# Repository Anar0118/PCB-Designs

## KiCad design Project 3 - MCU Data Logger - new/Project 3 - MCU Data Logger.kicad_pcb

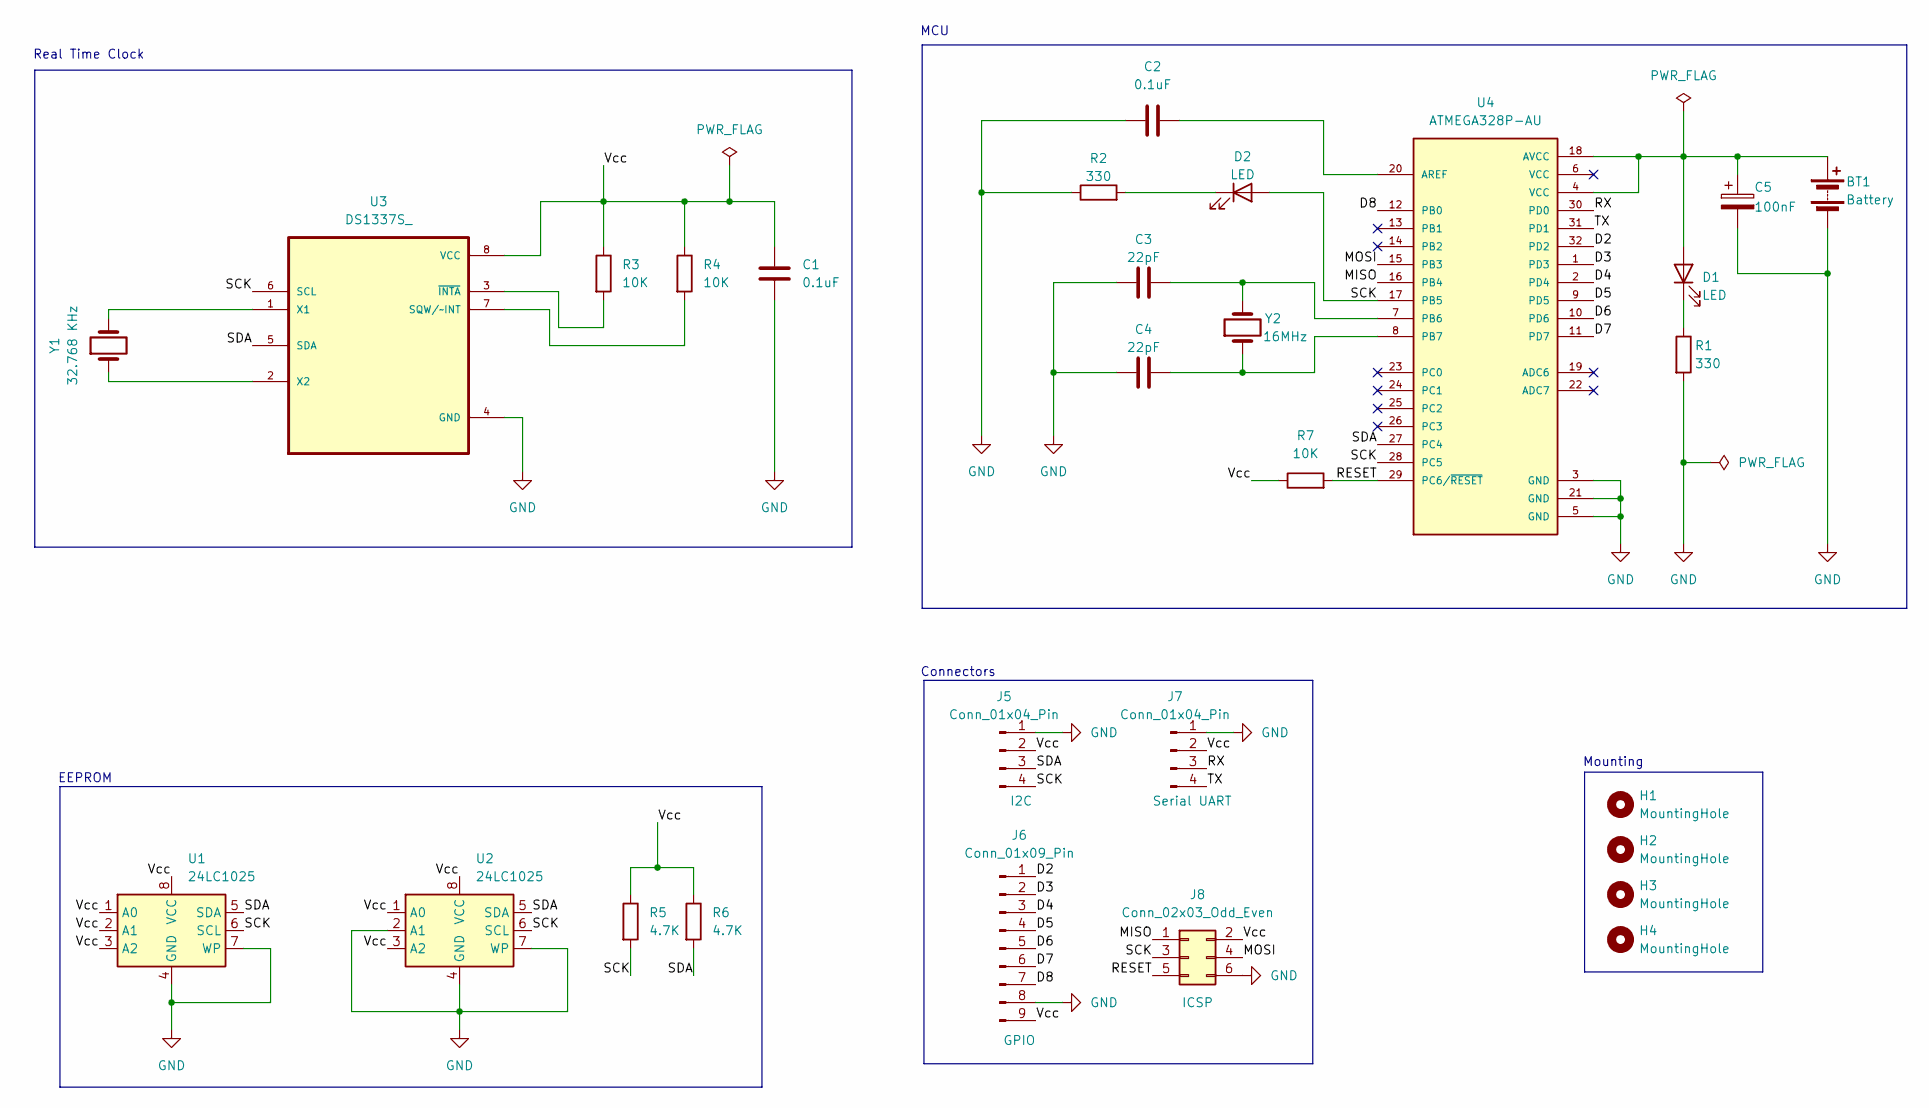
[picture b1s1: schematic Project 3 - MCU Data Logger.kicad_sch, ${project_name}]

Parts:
BT1: Battery; PinHeader_1x02_P2.54mm_Vertical
C1, C2: 0.1uF; C_0805_2012Metric
C3, C4: 22pF; C_0805_2012Metric
C5: 100nF; C_0805_2012Metric
D1, D2: LED; LED_0805_2012Metric
H1, H2, H3, H4: MountingHole; MountingHole_2.1mm
J5, J7: Conn_01x04_Pin; PinHeader_1x04_P2.54mm_Vertical
J6: Conn_01x09_Pin; PinHeader_1x09_P2.54mm_Vertical
J8: Conn_02x03_Odd_Even; PinHeader_2x03_P2.54mm_Vertical
R1, R2: 330; R_0805_2012Metric
R3, R4, R7: 10K; R_0805_2012Metric
R5, R6: 4.7K; R_0805_2012Metric
U1, U2: 24LC1025; SOIC-8_5.23x5.23mm_P1.27mm
U3: DS1337S_; SOIC127P600X175-8N
U4: ATMEGA328P-AU; QFP80P900X900X120-32N; PARTREV 8271A
Y1: 32.768 KHz; Crystal_SMD_5032-2Pin_5.0x3.2mm_HandSoldering
Y2: 16MHz; Crystal_SMD_5032-2Pin_5.0x3.2mm_HandSoldering

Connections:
/D2: J6.1, U4.32 (PD2)
/D3: J6.2, U4.1 (PD3)
/D4: J6.3, U4.2 (PD4)
/D5: J6.4, U4.9 (PD5)
/D6: J6.5, U4.10 (PD6)
/D7: J6.6, U4.11 (PD7)
/D8: J6.7, U4.12 (PB0)
/MISO: J8.1, U4.16 (PB4)
/MOSI: J8.4, U4.15 (PB3)
/RESET: J8.5, R7.2, U4.29 (PC6/~RESET)
/RX: J7.3, U4.30 (PD0)
/SCK: D2.2 (A), J5.4, J8.3, R5.2, U1.6 (SCL), U2.6 (SCL), U3.6 (SCL), U4.17 (PB5), U4.28 (PC5)
/SDA: J5.3, R6.2, U1.5 (SDA), U2.5 (SDA), U3.5 (SDA), U4.27 (PC4)
/TX: J7.4, U4.31 (PD1)
/Vcc: C1.1, J5.2, J6.9, J7.2, J8.2, R3.1, R4.1, R5.1, R6.1, R7.1, U1.1 (A0), U1.2 (A1), U1.3 (A2), U1.8 (VCC), U2.1 (A0), U2.3 (A2), U2.8 (VCC), U3.8 (VCC)
GND: BT1.2 (-), C1.2, C2.1, C3.1, C4.1, C5.2, J5.1, J6.8, J7.1, J8.6, R1.2, R2.1, U1.4 (GND), U1.7 (WP), U2.2 (A1), U2.4 (GND), U2.7 (WP), U3.4 (GND), U4.3 (GND), U4.5 (GND), U4.21 (GND)
unnamed: BT1.1 (+), C5.1, D1.2 (A), U4.4 (VCC), U4.18 (AVCC)
unnamed: D1.1 (K), R1.1
unnamed: D2.1 (K), R2.2
unnamed: R4.2, U3.7 (SQW/~INT)
unnamed: U3.1 (X1), Y1.2
unnamed: U3.2 (X2), Y1.1
unnamed: R3.2, U3.3 (~INTA)
unnamed: C2.2, U4.20 (AREF)
unnamed: C3.2, U4.7 (PB6), Y2.2
unnamed: C4.2, U4.8 (PB7), Y2.1

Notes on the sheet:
EEPROM
Mounting
MCU
Real Time Clock
Connectors

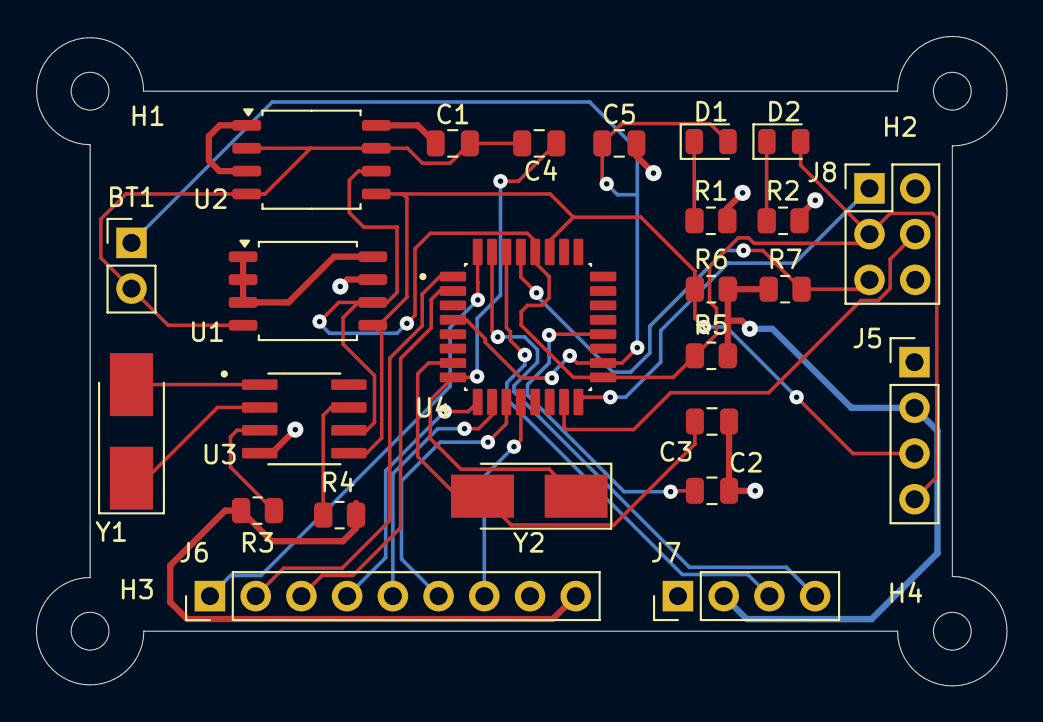
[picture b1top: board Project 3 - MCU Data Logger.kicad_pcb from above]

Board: 2 copper layers, 53.9 x 36.1 mm, 29 parts (0 on the bottom side), 26 nets.

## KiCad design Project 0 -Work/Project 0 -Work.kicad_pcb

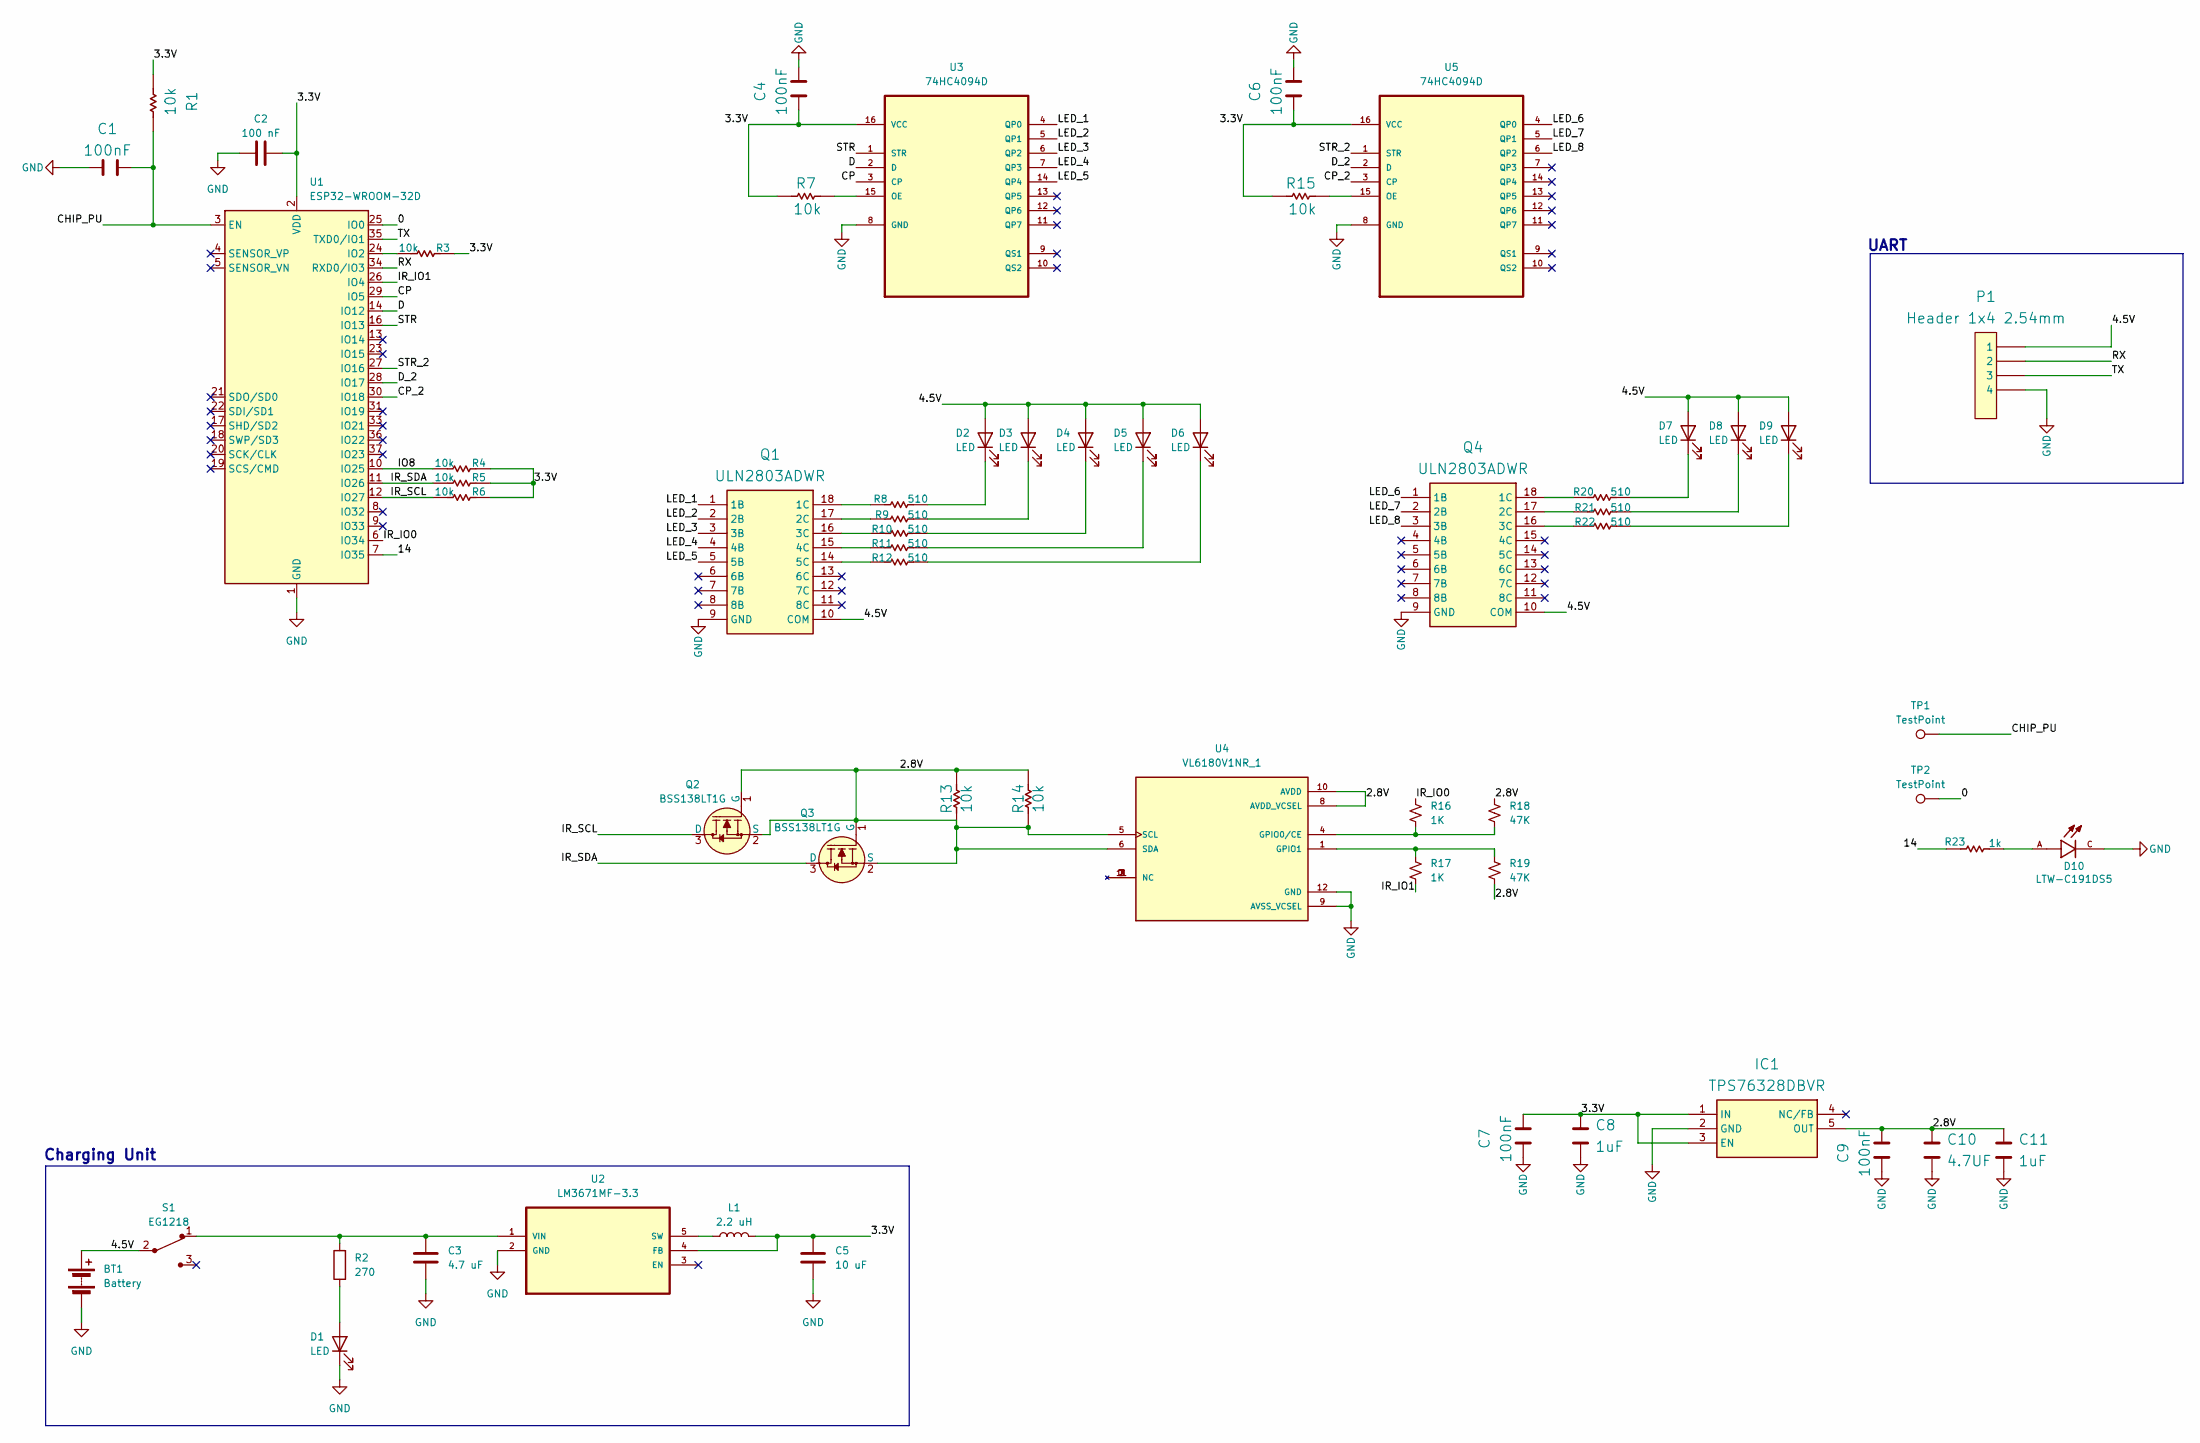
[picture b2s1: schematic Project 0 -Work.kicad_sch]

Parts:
BT1: Battery; BatteryHolder_Keystone_2479_3xAAA
C1, C4, C6, C7, C9: 100nF; C_0603_1608Metric
C2: 100 nF; C_0603_1608Metric
C3: 4.7 uF; C_0603_1608Metric
C5: 10 uF; C_0603_1608Metric
C8, C11: 1uF; C_1206_3216Metric
C10: 4.7UF; C_1206_3216Metric
D1, D2, D3, D4, D5, D6, D7, D8, D9: LED; LED_D3.0mm
D10: LTW-C191DS5; LEDC1608X65N
IC1: TPS76328DBVR; SOT-23-5; Manufacturer_Part_Number TPS76328DBVR; Mouser Part Number 595-TPS76328DBVR
L1: 2.2 uH; L_6.3x6.3_H3
P1: Header 1x4 2.54mm; PinSocket_2x02_P1.27mm_Vertical_SMD
Q1, Q4: ULN2803ADWR; SOIC-18W_7.5x11.6mm_P1.27mm; Manufacturer_Part_Number ULN2803ADWR
Q2, Q3: BSS138LT1G; SOT-23-3; MPN BSS138LT1G; Digi-Key_PN BSS138LT1GOSCT-ND
R1, R3, R4, R5, R6, R7, R13, R14, R15: 10k; R_0603_1608Metric
R2: 270; R_0603_1608Metric
R8, R9, R10, R11, R12, R20, R21, R22: 510; R_0603_1608Metric
R16, R17: 1K; R_0603_1608Metric
R18, R19: 47K; R_0603_1608Metric
R23: 1k; R_0603_1608Metric
S1: EG1218; Switch_Slide_11.6x4mm_EG1218; MPN EG1218; Digi-Key_PN EG1903-ND
TP1, TP2: TestPoint; TestPoint_Pad_D1.5mm
U1: ESP32-WROOM-32D
U2: LM3671MF-3.3; SOT95P284X122-5N; MPN LM3671MF-3.3
U3, U5: 74HC4094D; SOIC127P600X175-16N; MPN 74HC4094D
U4: VL6180V1NR_1; XDCR_VL6180V1NR_1; PARTREV A

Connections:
/0: TP2.1, U1.25 (IO0)
/2.8V: C9.2, C10.2, C11.2, IC1.5 (OUT), Q2.1 (G), Q2.2 (S), Q3.1 (G), Q3.2 (S), R13.1, R13.2, R14.1, R14.2, R18.2, R19.1, U4.5 (SCL), U4.6 (SDA), U4.8 (AVDD_VCSEL), U4.10 (AVDD)
/3.3V: C2.2, C4.1, C5.1, C6.1, C7.2, C8.2, IC1.1 (IN), IC1.3 (EN), L1.2, R1.1, R3.2, R4.2, R5.2, R6.2, R7.1, R15.1, U1.2 (VDD), U2.4 (FB), U3.16 (VCC), U5.16 (VCC)
/4.5V: BT1.1 (+), D2.2 (A), D3.2 (A), D4.2 (A), D5.2 (A), D6.2 (A), D7.2 (A), D8.2 (A), D9.2 (A), P1.1, Q1.10 (COM), Q4.10 (COM), S1.2
/14: R23.1, U1.7 (IO35)
/CHIP_PU: C1.2, R1.2, TP1.1, U1.3 (EN)
/CP: U1.29 (IO5), U3.3 (CP)
/CP_2: U1.30 (IO18), U5.3 (CP)
/D: U1.14 (IO12), U3.2 (D)
/D_2: U1.28 (IO17), U5.2 (D)
/IO8: R4.1, U1.10 (IO25)
/IR_IO0: R16.2, U1.6 (IO34)
/IR_IO1: R17.1, U1.26 (IO4)
/IR_SCL: Q2.3 (D), R6.1, U1.12 (IO27)
/IR_SDA: Q3.3 (D), R5.1, U1.11 (IO26)
/LED_1: Q1.1 (1B), U3.4 (QP0)
/LED_2: Q1.2 (2B), U3.5 (QP1)
/LED_3: Q1.3 (3B), U3.6 (QP2)
/LED_4: Q1.4 (4B), U3.7 (QP3)
/LED_5: Q1.5 (5B), U3.14 (QP4)
/LED_6: Q4.1 (1B), U5.4 (QP0)
/LED_7: Q4.2 (2B), U5.5 (QP1)
/LED_8: Q4.3 (3B), U5.6 (QP2)
/RX: P1.2, U1.34 (RXD0/IO3)
/STR: U1.16 (IO13), U3.1 (STR)
/STR_2: U1.27 (IO16), U5.1 (STR)
/TX: P1.3, U1.35 (TXD0/IO1)
GND: BT1.2 (-), C1.1, C2.1, C3.2, C4.2, C5.2, C6.2, C7.1, C8.1, C9.1, C10.1, C11.1, D1.1 (K), D10.C, IC1.2 (GND), P1.4, Q1.9 (GND), Q4.9 (GND), U1.1 (GND), U1.15 (GND), U1.38 (GND), U1.39 (GND), U2.2 (GND), U3.8 (GND), U4.9 (AVSS_VCSEL), U4.12 (GND), U5.8 (GND)
unnamed: D1.2 (A), R2.1
unnamed: D2.1 (K), R8.2
unnamed: D3.1 (K), R9.2
unnamed: D4.1 (K), R10.2
unnamed: D5.1 (K), R11.2
unnamed: D6.1 (K), R12.2
unnamed: D7.1 (K), R20.2
unnamed: D8.1 (K), R21.2
unnamed: D9.1 (K), R22.2
unnamed: D10.A, R23.2
unnamed: Q1.18 (1C), R8.1
unnamed: Q1.17 (2C), R9.1
unnamed: Q1.16 (3C), R10.1
unnamed: Q1.15 (4C), R11.1
unnamed: Q1.14 (5C), R12.1
unnamed: Q4.18 (1C), R20.1
unnamed: Q4.17 (2C), R21.1
unnamed: Q4.16 (3C), R22.1
unnamed: R3.1, U1.24 (IO2)
unnamed: L1.1, U2.5 (SW)
unnamed: C3.1, R2.2, S1.1, U2.1 (VIN)
unnamed: R7.2, U3.15 (OE)
unnamed: R16.1, R18.1, U4.4 (GPIO0/CE)
unnamed: R17.2, R19.2, U4.1 (GPIO1)
unnamed: R15.2, U5.15 (OE)

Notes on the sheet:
Charging Unit
UART

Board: 2 copper layers, 60 parts (3 on the bottom side), 53 nets, no tracks yet.

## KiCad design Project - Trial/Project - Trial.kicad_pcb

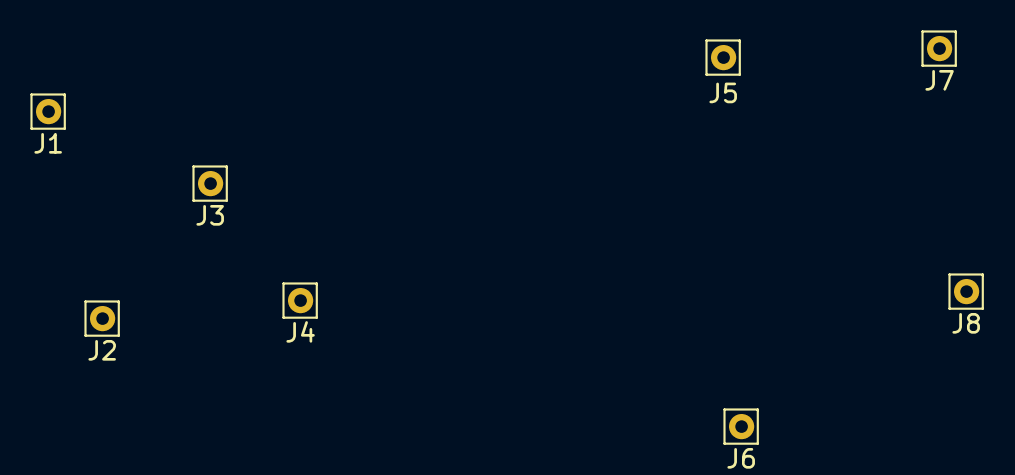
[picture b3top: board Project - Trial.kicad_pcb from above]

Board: 2 copper layers, 8 parts (0 on the bottom side), 2 nets, no tracks yet.

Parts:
J1, J2, J3, J4, J5, J6, J7, J8: Conn_01x01_Socket; Pin_D0.7mm_L6.5mm_W1.8mm_FlatFork

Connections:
/net_1: J1.1, J2.1, J3.1, J4.1
/net_2: J5.1, J6.1, J7.1, J8.1

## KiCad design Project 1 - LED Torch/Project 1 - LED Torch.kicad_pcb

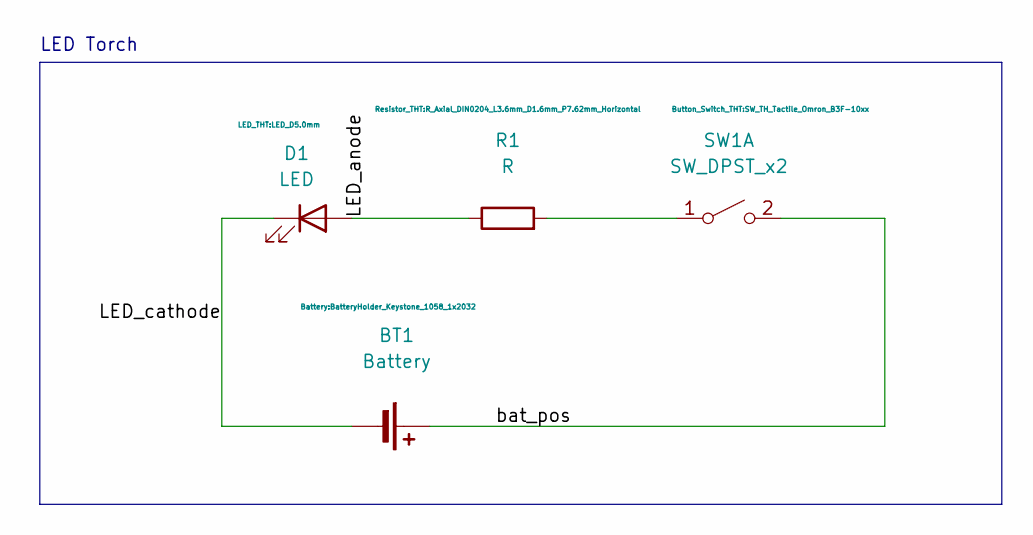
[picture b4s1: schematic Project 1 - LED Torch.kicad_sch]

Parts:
BT1: Battery; BatteryHolder_Keystone_1058_1x2032
D1: LED; LED_D5.0mm
R1: R; R_Axial_DIN0204_L3.6mm_D1.6mm_P7.62mm_Horizontal
SW1: SW_DPST_x2; SW_TH_Tactile_Omron_B3F-10xx

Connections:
/LED_anode: D1.2 (A), R1.1
/LED_cathode: BT1.2 (-), D1.1 (K)
/bat_pos: BT1.1 (+), SW1.2 (B)
unnamed: R1.2, SW1.1 (A)

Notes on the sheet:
LED Torch

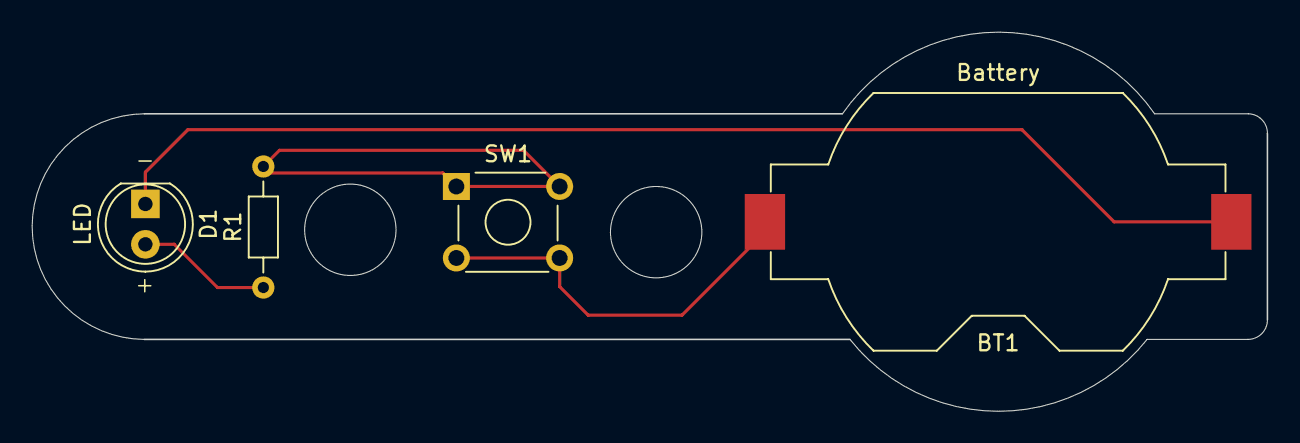
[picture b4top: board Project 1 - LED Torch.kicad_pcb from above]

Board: 2 copper layers, 77.7 x 23.8 mm, 4 parts (0 on the bottom side), 4 nets.

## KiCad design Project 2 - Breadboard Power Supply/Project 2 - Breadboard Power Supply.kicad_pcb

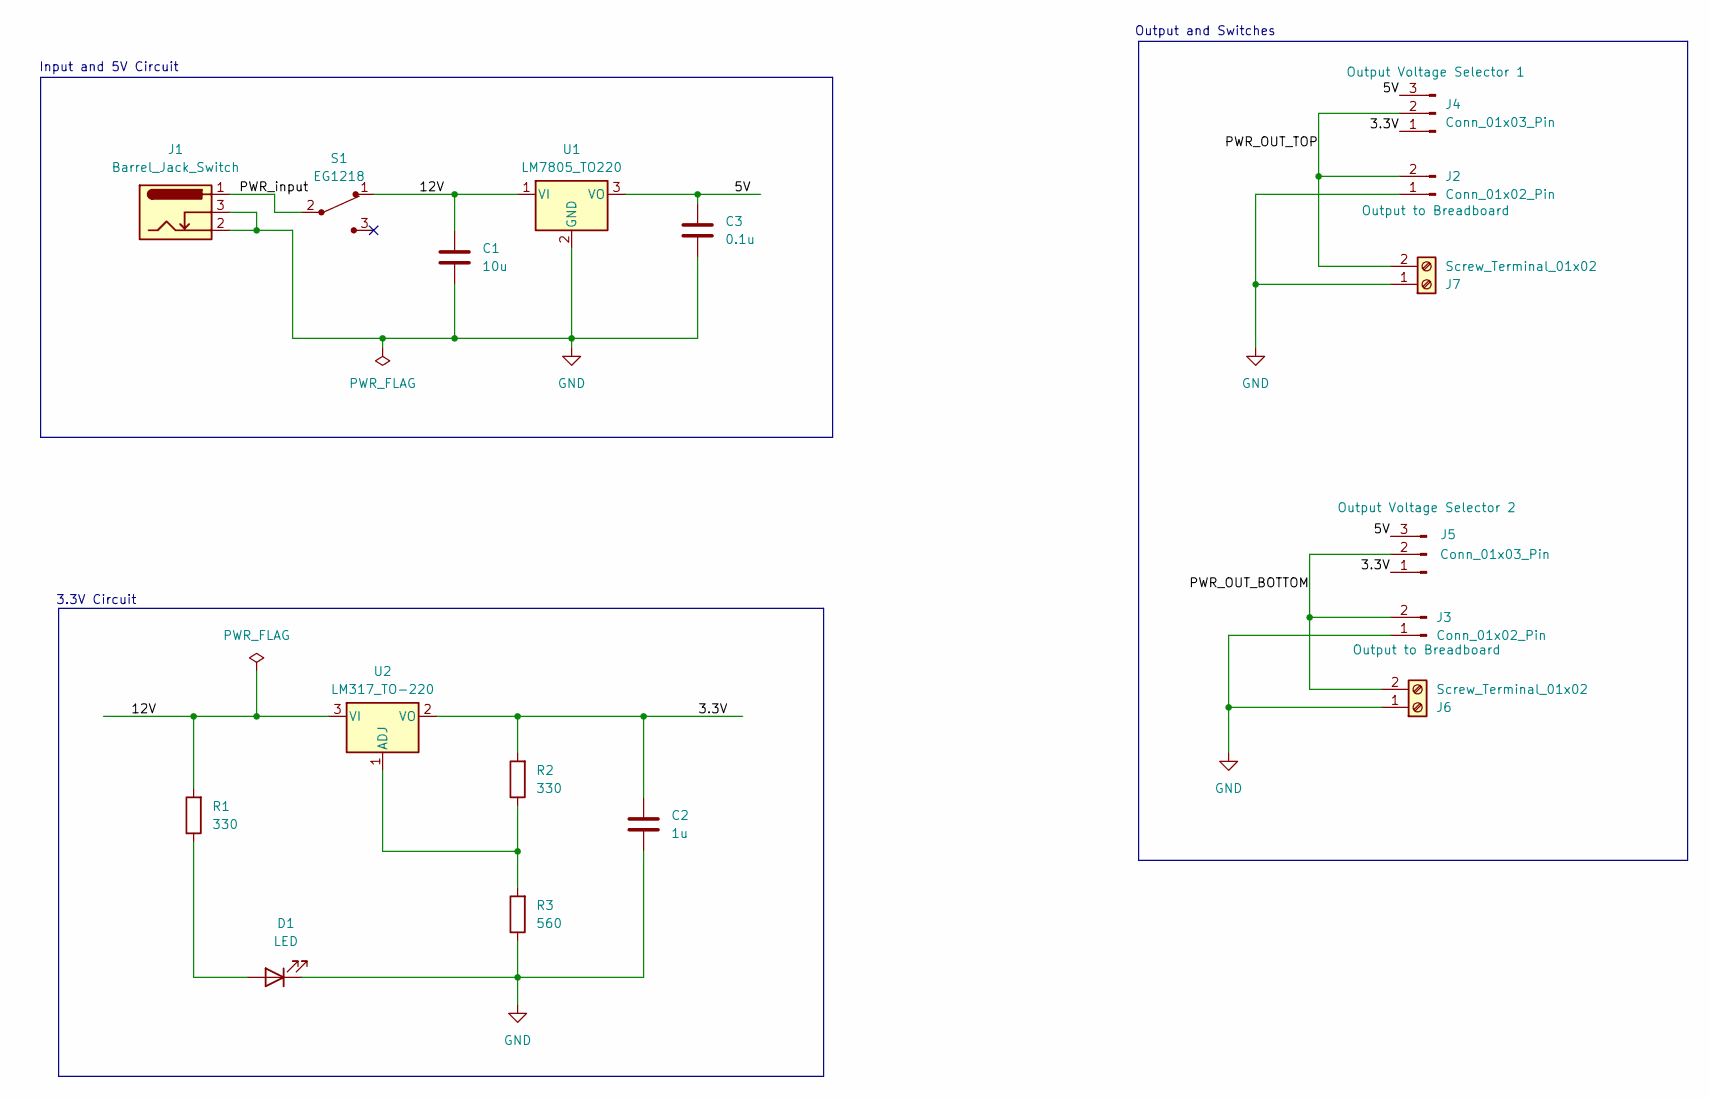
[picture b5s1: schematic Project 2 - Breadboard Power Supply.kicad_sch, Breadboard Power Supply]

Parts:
C1: 10u; C_Disc_D3.0mm_W1.6mm_P2.50mm
C2: 1u; C_Disc_D3.0mm_W1.6mm_P2.50mm
C3: 0.1u; C_Disc_D3.0mm_W1.6mm_P2.50mm
D1: LED; LED_D5.0mm
J1: Barrel_Jack_Switch; BarrelJack_Horizontal
J2, J3: Conn_01x02_Pin; PinHeader_1x02_P2.54mm_Vertical
J4, J5: Conn_01x03_Pin; PinHeader_1x03_P2.54mm_Vertical
J6, J7: Screw_Terminal_01x02; TerminalBlock_bornier-2_P5.08mm
R1, R2: 330; R_Axial_DIN0204_L3.6mm_D1.6mm_P7.62mm_Horizontal
R3: 560; R_Axial_DIN0204_L3.6mm_D1.6mm_P7.62mm_Horizontal
S1: EG1218; Switch_Slide_11.6x4mm_EG1218; MPN EG1218; Digi-Key_PN EG1903-ND
U1: LM7805_TO220; TO-220-3_Vertical
U2: LM317_TO-220; TO-220-3_Vertical

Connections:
/3.3V: C2.2, J4.1, J5.1, R2.2, U2.2 (VO)
/5V: C3.1, J4.3, J5.3, U1.3 (VO)
/12V: C1.1, R1.2, S1.1, U1.1 (VI), U2.3 (VI)
/PWR_OUT_BOTTOM: J3.2, J5.2, J6.2
/PWR_OUT_TOP: J2.2, J4.2, J7.2
/PWR_input: J1.1, S1.2
GND: C1.2, C2.1, C3.2, D1.1 (K), J1.2, J1.3, J2.1, J3.1, J6.1, J7.1, R3.1, U1.2 (GND)
unnamed: D1.2 (A), R1.1
unnamed: R2.1, R3.2, U2.1 (ADJ)

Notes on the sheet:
3.3V Circuit
Input and 5V Circuit
Output and Switches

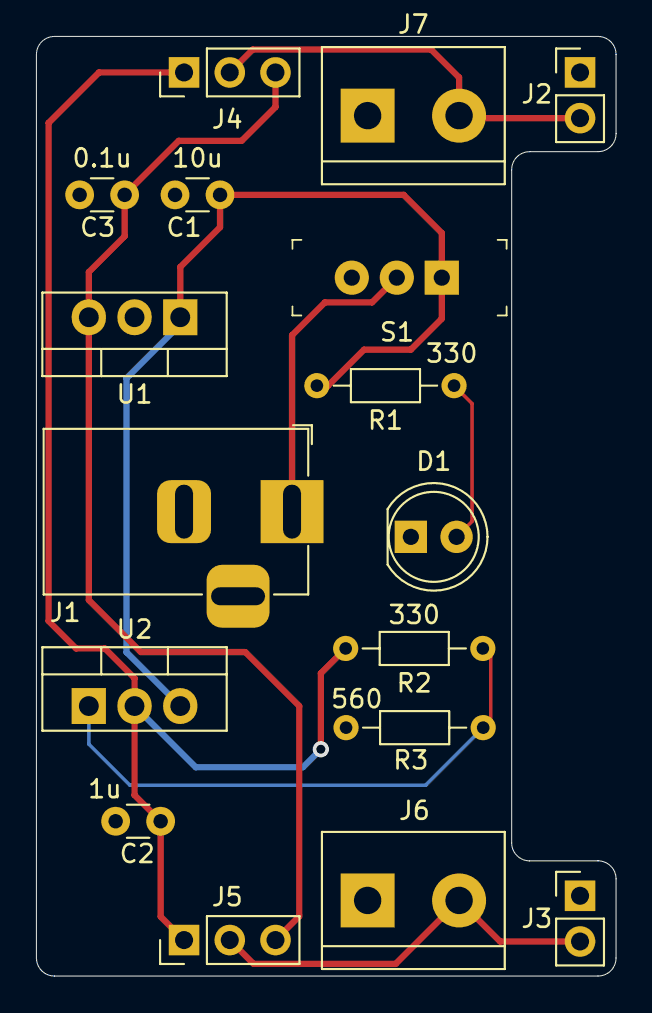
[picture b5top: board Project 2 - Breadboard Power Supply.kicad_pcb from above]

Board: 2 copper layers, 32.2 x 52.2 mm, 17 parts (0 on the bottom side), 9 nets.

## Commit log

2025-03-28 Adding PCB Design Projects
2025-03-28 Added Project 3
2025-03-28 Renamed Project 3
2025-03-28 Added Project 3 properly
